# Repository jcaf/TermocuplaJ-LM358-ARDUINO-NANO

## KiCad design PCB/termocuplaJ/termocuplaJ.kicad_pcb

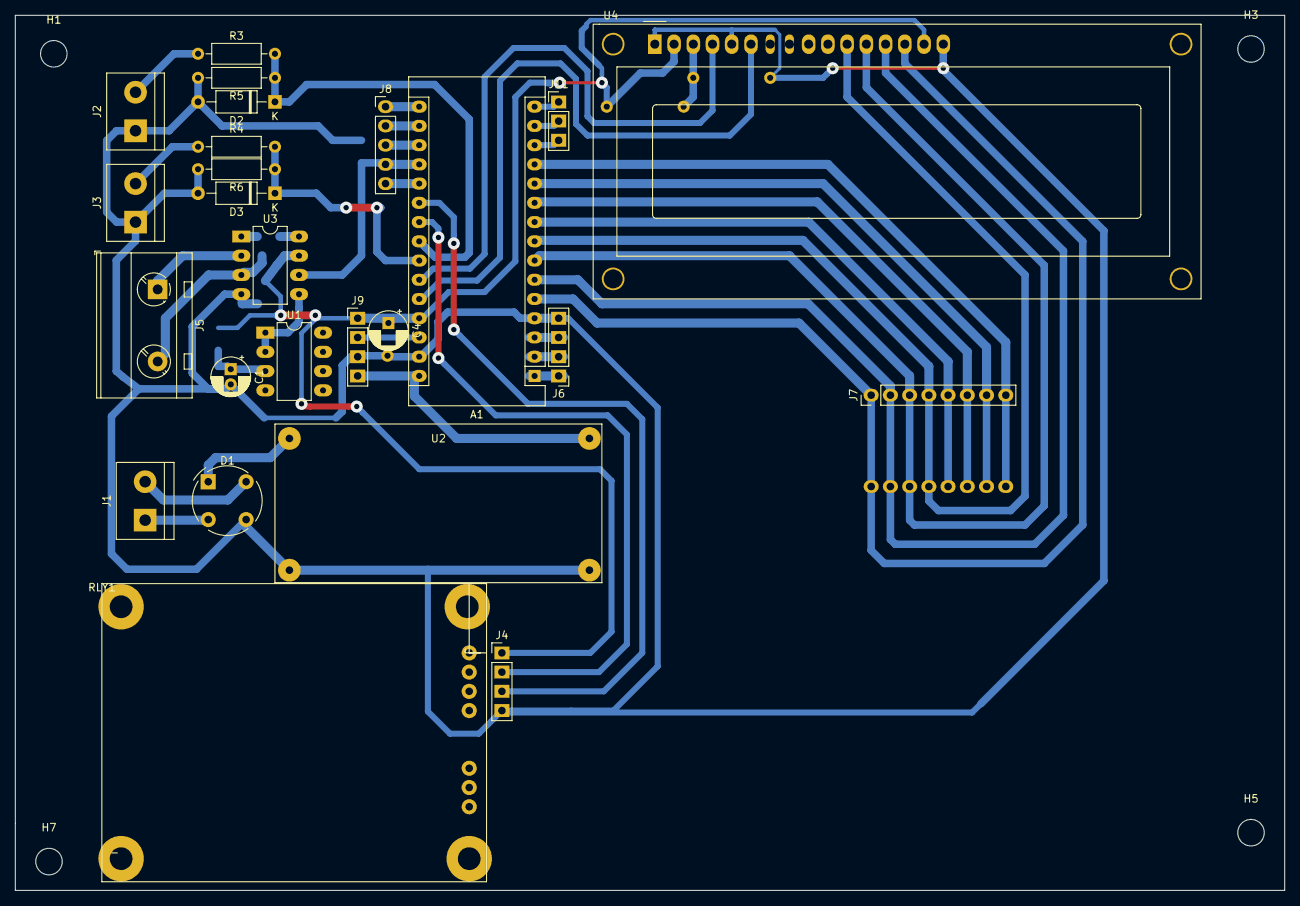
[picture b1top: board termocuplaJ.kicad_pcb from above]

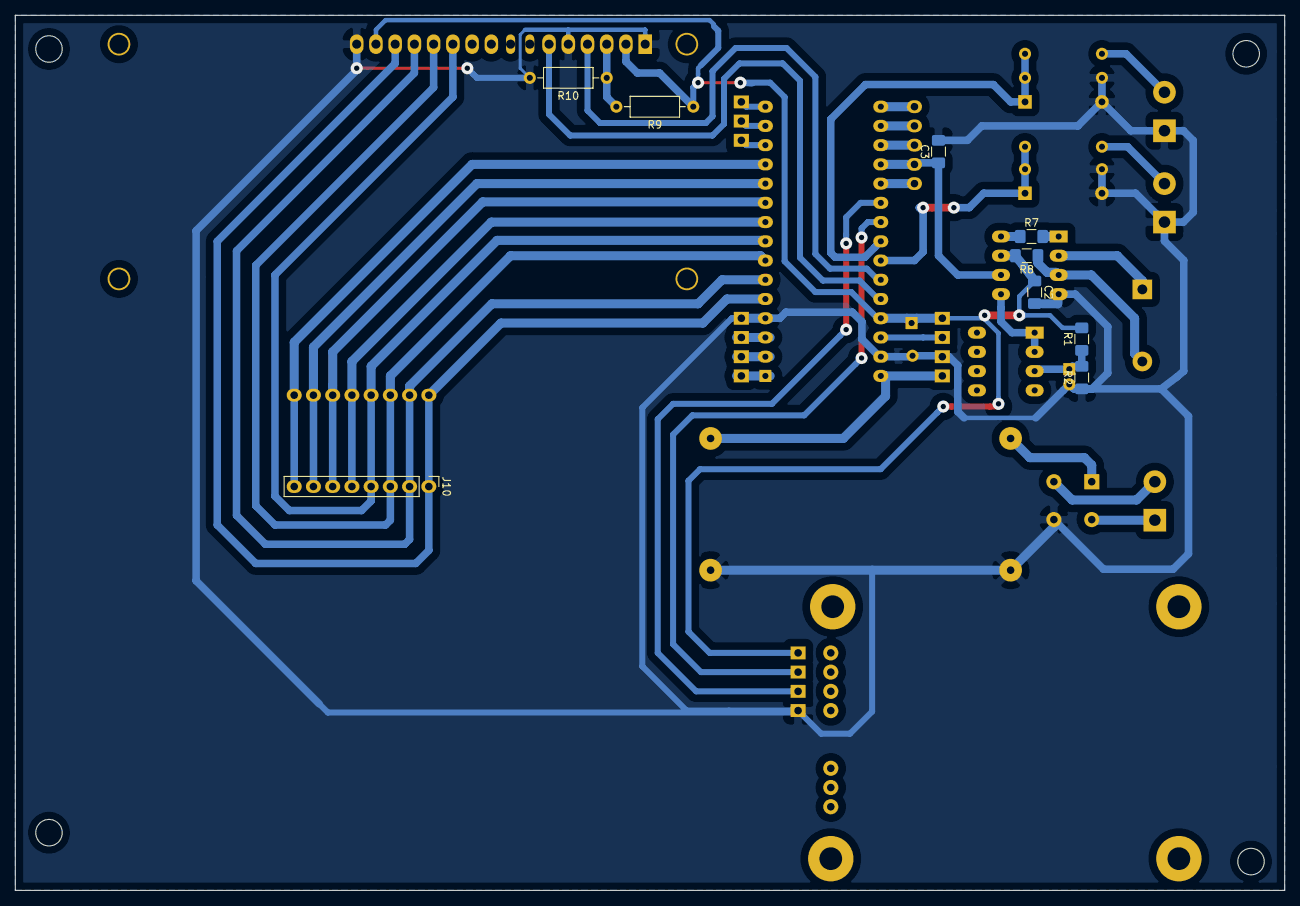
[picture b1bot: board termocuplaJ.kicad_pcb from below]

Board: 2 copper layers, 167.6 x 115.6 mm, 38 parts (9 on the bottom side), 41 nets.

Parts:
A1: Arduino_Nano_v2.x; Arduino_Nano
C1: 1uF/16V; CP_Radial_D5.0mm_P2.00mm
C2, C3: 0.1uF; C_1206_3216Metric_Pad1.42x1.75mm_HandSolder
C4: 100uF/16V; CP_Radial_D5.0mm_P2.00mm
D1: W04G; Diode_Bridge_Round_D9.0mm
D2, D3: 5.1V; D_A-405_P10.16mm_Horizontal
H1, H3, H5, H7: MountingHole; MountingHole_3.5mm
J1, J2, J3: Screw_Terminal_01x02; TerminalBlock_bornier-2_P5.08mm
J4: 2-relay-module; PinHeader_1x04_P2.54mm_Vertical
J5: J-THERMO; TerminalBlock_MetzConnect_Type703_RT10N02HGLU_1x02_P9.52mm_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
J6, J9: Conn_01x04_Male; PinHeader_1x04_P2.54mm_Vertical
J7, J10: Keypad4x4; PinHeader_1x08_P2.54mm_Vertical
J8: Conn_01x05_Male; PinHeader_1x05_P2.54mm_Vertical
J11: Conn_01x03_Male; PinHeader_1x03_P2.54mm_Vertical
R1, R2, R8: 10k; R_1206_3216Metric_Pad1.42x1.75mm_HandSolder
R3, R4, R9: 10k; R_Axial_DIN0207_L6.3mm_D2.5mm_P10.16mm_Horizontal
R5, R6: 2.7k; R_Axial_DIN0207_L6.3mm_D2.5mm_P10.16mm_Horizontal
R7: 499; R_1206_3216Metric_Pad1.42x1.75mm_HandSolder
R10: 1.5-2k; R_Axial_DIN0207_L6.3mm_D2.5mm_P10.16mm_Horizontal
RLY1: 2-Relay-Module
U1: LM358; DIP-8_W7.62mm_LongPads
U2: LM2596DC-DC-StepDown; LM2596-DC-DC-StepDown
U3: INA129; DIP-8_W7.62mm_LongPads
U4: RC1602A; WC1602A

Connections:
+3V3: A1.17, J8.2
+5V: A1.27, C2.1, C4.1, J4.1, J9.1, R1.2, R8.2, R9.1, U3.7, U4.2, U4.15
+9V: A1.30, J9.4, U2.4
/A1: A1.20, J8.5
/COL1: A1.9, J7.5, J10.5
/COL2: A1.10, J7.6, J10.6
/COL3: A1.11, J7.7, J10.7
/COL4: A1.12, J7.8, J10.8
/FIL1: A1.5, J7.1, J10.1, U4.14
/FIL2: A1.6, J7.2, J10.2, U4.13
/FIL3: A1.7, J7.3, J10.3, U4.12
/FIL4: A1.8, J7.4, J10.4, U4.11
/INPUT1: A1.23, D2.1, R3.2, R5.1
/INPUT2: A1.24, D3.1, R4.2, R6.1
/LCD_E: A1.26, U4.6
/LCD_RS: A1.25, U4.4
/MISO: A1.15, J11.1
/MOSI: A1.14, J11.2
/RED(T+): J5.2, R8.1, U3.3
/REF: A1.18, J8.3
/RELAY1: A1.21, J4.3
/RELAY2: A1.22, J4.2
/RST3: A1.3, J6.3
/RST28: A1.28, J9.2
/RXD: A1.2, J6.2
/SCK: A1.16, J8.1
/SS: A1.13, J11.3
/TERMO: A1.19, C3.1, J8.4, U3.6
/TXD: A1.1, J6.1
/YELLOW(T-): J5.1, U3.2
GND: A1.4, A1.29, C1.2, C2.2, C3.2, C4.2, D1.3, D2.2, D3.2, J2.1, J3.1, J4.4, J6.4, J9.3, R2.1, R5.2, R6.2, R10.2, U2.2, U2.3, U3.4, U4.1, U4.5, U4.16
unnamed: C1.1, R1.1, R2.2, U1.3
unnamed: D1.1, U2.1
unnamed: D1.2, J1.1
unnamed: D1.4, J1.2
unnamed: J2.2, R3.1
unnamed: J3.2, R4.1
unnamed: R7.1, U3.8
unnamed: R7.2, U3.1
unnamed: R9.2, R10.1, U4.3
unnamed: U1.1, U1.2, U3.5

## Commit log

2019-04-10 solid relay
2019-04-11 Optimized for mechanical relay CYCLE TIME = 10s
2019-04-11 antes de cambiar el timer a min:sec
2019-04-11 Timer changed to MIN:SEC ok!
2019-04-12 To release!
2019-04-15 Reset function is a new piece!
2019-04-20 El ultimo commit, antes de pasar todo a C, nada de arduino. Tambien cambio de nombre a la carpeta
2019-04-21 added.. const to ..
2019-05-01 Antes de actualizar con lo realizado en la nueva version
2019-05-01 Con todos los cambios del proyecto basado en el atmega328p
